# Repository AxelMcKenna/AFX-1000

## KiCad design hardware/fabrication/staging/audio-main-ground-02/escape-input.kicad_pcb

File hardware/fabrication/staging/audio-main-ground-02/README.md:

# AC04 — routed local cells and complete placed-ground continuity

| Top copper | Bottom copper, viewed from below |
| --- | --- |
|  |  |

**The board is not ready for fabrication.** It remains a 150 × 63 × 1.6 mm
four-layer candidate with 328 assigned electrical footprints, four bare test
pads included, and six proposed mounts. U201/ES9292QPRO has no approved land
assignment. Its marked reserve is not a substitute footprint.

**All 131 declared local signal/supply endpoints, all twenty declared local
ground-return pairs, and all 200 placed AGND pads are native-connected.**
The ground reference is protected input terminal J701.2. The earlier 724 open
connections are reduced to **393**; global signal and supply routing is still
unfinished. In2 is reserved for later distribution and has no adopted plane.

| Isolated Linux KiCad 10.0.7 check | Result |
| --- | --- |
| Geometry findings | **0** |
| ERC findings | **0** |
| Schematic parity | **1: missing U201 footprint** |
| Native open connections, uncapped | **393** |
| Ignored DRC / ERC categories | **0 / 0** |
| Tracks / conventional vias | **448 / 199** |
| Placed ground terminals connected to J701.2 | **200 / 200** |

The In1 AGND reference has **8,182.35 mm²** of stored native-filled copper.
Twelve plane openings protect the FDA input/output nodes and the OPA1612
summing nodes on both inner layers. Six full-layer copper exclusions retain
the proposed mounting-hardware allocations. The codec's existing all-layer
reserve remains clear. The [THS4551 layout guidance](https://www.ti.com/lit/gpn/ths4551)
calls for continuous references with openings around sensitive input/output
pins; [OPA1612 layout guidance](https://www.ti.com/lit/ds/symlink/opa1612.pdf)
also addresses grounding and local feedback placement. The 0.5 mm pad and
0.6 mm trace-centre opening margins are project allocations, not manufacturer
specified dimensions or a measured parasitic/stability result.

The 179 added ground vias use 0.60 mm copper lands and 0.30 mm drills. Together
with the twenty retained local signal/supply vias, the fresh native land screen
finds a minimum **0.170 mm** drill-edge-to-SMD-copper gap across both faces,
including same-net lands. No via drill intersects an SMD solder land. Mask
registration/tenting, stencil, plating and the actual stack still need supplier
acceptance. The 182 ground branches include reuse of existing vias. All normal
escape traces retain a 3.5 mm budget; supervisor U205.2 uses a 4.75 mm trace
within its original 5.6 mm local-ground construction allowance. Width remains
0.20 mm. Those lengths exclude travel through the via barrel and do not qualify
current capacity, ground noise or high-frequency return performance.

All amplifier poses and direct compensation capacitor tracks remain unchanged.
The [preceding local rework](../audio-main-local-routing-03/README.md) moves three
unrouted parts. This successor additionally rotates C310 180° in the same body
courtyard, placing its ground terminal outside the congested plane opening.
Its signal terminal remains on the original net. Every conditional body,
floor, upper-board, solder-tail, codec-reserve and support receiving constraint
is renewed; actual mating parts, fasteners, case details and tolerances remain
unapproved. Bare test pads still need explicit non-fitted-copper BOM treatment.

The [independent handoff replay](routing-handoff.json) binds actual copper,
native refill output, per-terminal connectivity and fresh pad geometry. It
checks all pre-existing analog copper, every added branch, all actual drills,
the protected plane openings, and complete ground-terminal coverage. Plane
boundaries use a one-nanometre comparison tolerance matching coordinate
serialization; no copper-clearance or local analog length budget is relaxed.
Executed generation/review source snapshots are retained separately so later
tool development does not rewrite historical evidence.

**Connectivity is not complete power/return, noise, stability, thermal or
manufacturing qualification.** The remaining 393 connections, ESS package and
raw-interface data, physical ADC stars, final parts and harness/mates/supports,
installed power/fault/thermal analysis, inspected Gerber/drill/BOM/placement
outputs and bounded first-article plan must be completed before release. No
supplier request, board order or native Mac CAD launch is made by this work.

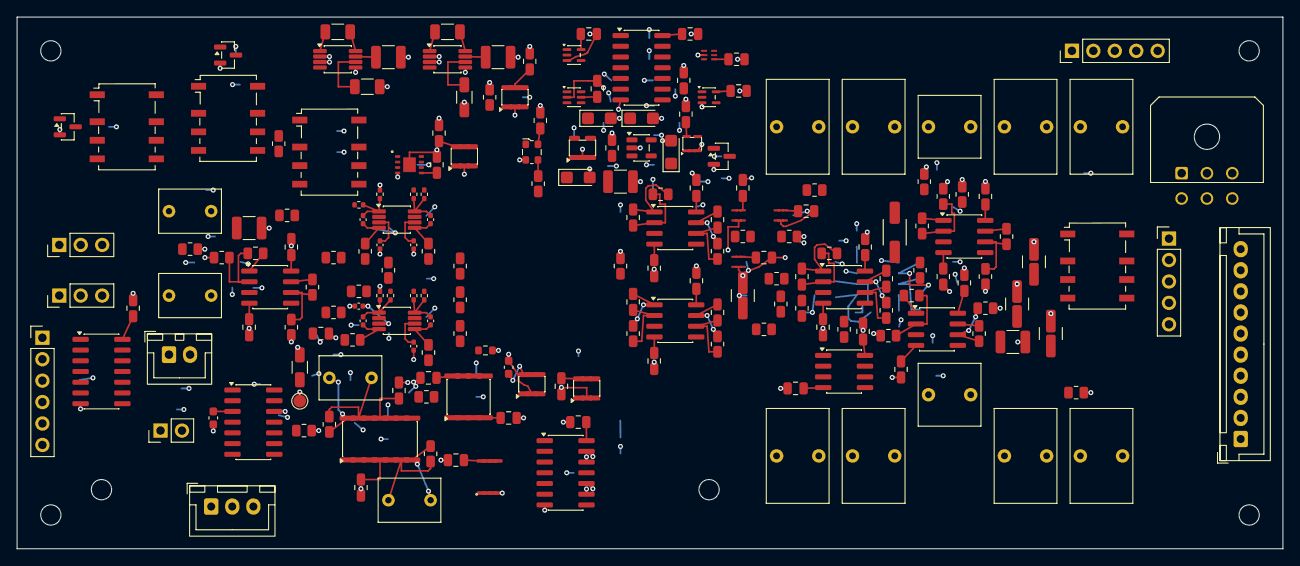
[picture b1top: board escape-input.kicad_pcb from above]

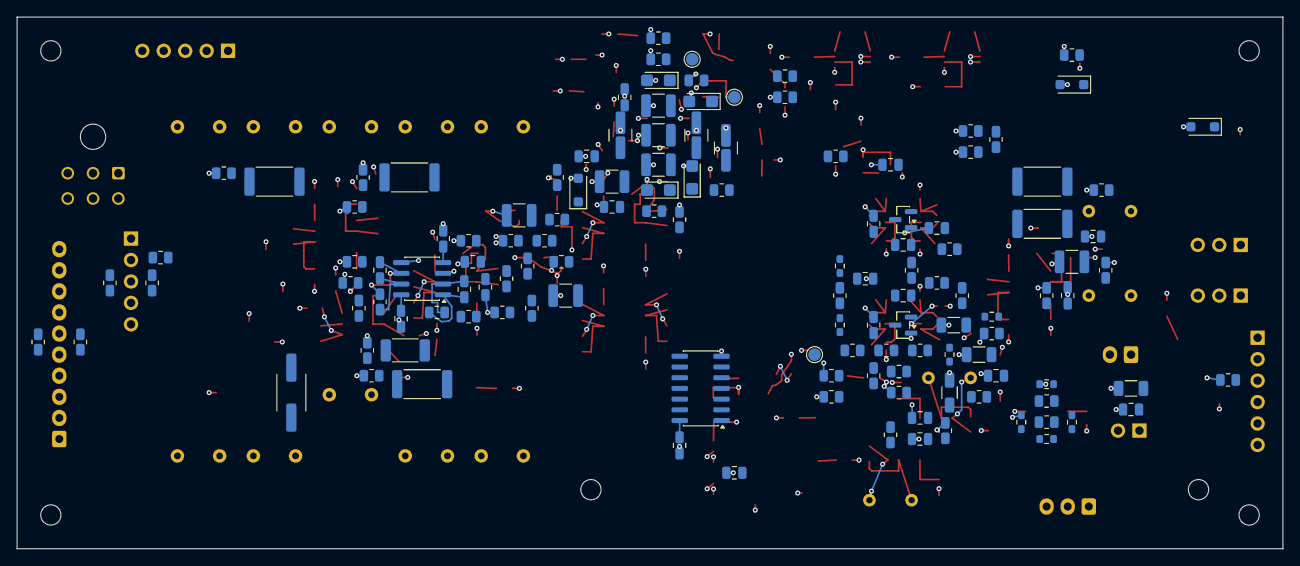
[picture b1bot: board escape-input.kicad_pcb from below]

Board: 4 copper layers, 150.0 x 63.0 mm, 334 parts (129 on the bottom side), 176 nets.

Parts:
C101, C102, C115, C116: 1pF C0G +/-0.1pF; C_0402_1005Metric
C103, C117: 47pF C0G 5%; C_0805_2012Metric
C104, C105, C118, C119: 22pF C0G 5%; C_0805_2012Metric
C106, C120: 100nF 25V X7R; C_0805_2012Metric
C107, C121: 1uF 63V film 10%; C_Rect_L7.2mm_W5.0mm_P5.00mm
C108, C122: 10uF 16V X7R; C_1206_3216Metric
C109, C123: 47uF 25V X7S; C_1210_3225Metric
C110, C111, C124, C125: 47uF 6.3V X7S; C_1206_3216Metric
C112, C126: 2.2uF 16V X7R; C_0805_2012Metric
C113, C114, C127, C128: 100nF 16V X7R; C_0402_1005Metric
C129, C130, C131, C132, C220, C221, C222, C223, C224, C225, C226, C228, C229, C311, C312, C313, C314, C315, C316, C317, C318, C323, C324, C405, C406, C505, C506, C507, C508: 100nF 50V X7R; C_0805_2012Metric
C133, C134: 10uF 50V X7R; C_1206_3216Metric
C135, C136: 100nF 16V X7R; C_0603_1608Metric
C201, C202, C205: 1uF 10V X7R 10%; C_0805_2012Metric
C203, C210, C212, C214: 100nF 50V C0G 5%; C_1210_3225Metric
C204, C206, C207, C208, C209, C211, C213, C215: 1uF 10V tantalum 10%; CP_EIA-3216-18_Kemet-A
C216, C218, C227: 2.2uF 25V X7R 10%; C_1210_3225Metric
C217, C219: 10uF 16V X7R 10%; C_1210_3225Metric
C230, C231, C232, C610, C611, C612: 100nF 16V X7R; C_0805_2012Metric
C301, C302, C306, C307: 510pF 50V C0G 2%; C_0805_2012Metric
C303, C308: 51pF 50V C0G 2%; C_0805_2012Metric
C304, C305, C309, C310: 1nF 50V C0G 1%; C_0805_2012Metric
C319, C320, C509, C510, C511, C512: 10uF 50V X7R; C_1210_3225Metric
C321, C322: 2.2uF film 63V 10%; C_Rect_L7.2mm_W7.2mm_P5.00mm_FKS2_FKP2_MKS2_MKP2
C401, C403: 1uF film 63V 10%; C_Rect_L7.2mm_W5.0mm_P5.00mm
C402, C404: 47pF 50V C0G 5%; C_0805_2012Metric
C407, C408: 10uF 50V X7R 10%; C_1210_3225Metric
C501, C502, C503, C504, C513, C514, C515, C516: 4.7uF film 63V 10%; C_Rect_L7.2mm_W11.0mm_P5.00mm_FKS2_FKP2_MKS2_MKP2
C601: 150pF C0G 5%; C_0805_2012Metric
C602, C603, C604, C605, C606: 100nF X7R; C_0805_2012Metric
C607: 1uF 16V X7R; C_0805_2012Metric
C608: 22uF 16V X7R; C_1206_3216Metric
C609: 1uF 16V X7R 10%; C_0805_2012Metric
D101, D102: BAT54S,215; SOT-23
D601, D602, D603: SMF9.0A; D_SOD-123F
H1, H2, H3, H4: M2_CLEARANCE; M2_Clearance
H5, H6: M2_SHARED_SUPPORT; M2_Clearance
J203, J603: Conn_01x05; PinHeader_1x05_P2.54mm_Vertical
J402: B10B-XH-A(LF)(SN); JST_XH_B10B-XH-A_1x10_P2.50mm_Vertical
J403: B3B-XH-A(LF)(SN); JST_XH_B3B-XH-A_1x03_P2.50mm_Vertical
J602: Conn_01x06; PinHeader_1x06_P2.54mm_Vertical
J606: Conn_01x02; PinHeader_1x02_P2.54mm_Vertical
J607, J608: Conn_01x03; PinHeader_1x03_P2.54mm_Vertical
J701: 43045-0600; Molex_Micro-Fit_3.0_43045-0600_2x03_P3.00mm_Horizontal
J702: B2B-XH-A(LF)(SN); JST_XH_B2B-XH-A_1x02_P2.50mm_Vertical
K401, K503, K601, K602: G6K-2F-Y DC5; Relay_DPDT_Omron_G6K-2F-Y
Q601, Q602, Q603: AO3400A; SOT-23
R101, R102, R117, R118: 2.49k 0.05%; R_0402_1005Metric
R103, R104, R119, R120: 1.21k 0.05%; R_0402_1005Metric
R105, R106, R121, R122: 3.3R 1%; R_0805_2012Metric
R107, R123: 1M 1%; R_0805_2012Metric
R108, R109, R124, R125: 100k 0.01%; R_0805_2012Metric
R110, R111, R126, R127, R212: 10k 0.1%; R_0805_2012Metric
R112, R128: 10M 1%; R_0805_2012Metric
R113, R129, R203, R204, R601, R606: 10k 1%; R_0805_2012Metric
R114, R130, R205, R206, R603, R604, R605, R607, R615: 47k 1%; R_0805_2012Metric
R115, R131: 68k 1%; R_0805_2012Metric
R116, R132: 0.1R 1%; R_0805_2012Metric
R133: 1k 1%; R_0805_2012Metric
R134, R136: 100k 0.01%; R_0603_1608Metric
R135, R137, R139, R141: 10k 0.01%; R_0603_1608Metric
R138: 161k 0.01%; R_0805_2012Metric
R140: 240k 0.01%; R_0805_2012Metric
R142, R143: 10k 1%; R_0603_1608Metric
R144: 100k 1%; R_0603_1608Metric
R201, R202: 2k 1%; R_0805_2012Metric
R207, R208, R209, R210, R517, R518, R602, R617, R618: 100k 1%; R_0805_2012Metric
R211: 27.7k 0.1%; R_0805_2012Metric
R213, R214, R215, R216: 33 1%; R_0805_2012Metric
R301, R302, R313, R314: 1.8k 0.1%; R_0805_2012Metric
R303, R304, R315, R316: 4.3 1%; R_0805_2012Metric
R305, R306, R317, R318: 100k 0.1%; R_0805_2012Metric
R307, R319: 1.2M 0.1%; R_0805_2012Metric
R308, R309, R310, R311, R320, R321, R322, R323: 499 0.01%; R_0805_2012Metric
R312, R324, R407, R414: 33.2 0.1%; R_0805_2012Metric
R325, R326, R401, R408: 33.2k 0.1%; R_0805_2012Metric
R327, R328: 2.74k 0.1% 0.5W; R_2010_5025Metric
R402, R409: 13.7k 0.1%; R_0805_2012Metric
R403, R410: 4.99k 0.1% 1W; R_2512_6332Metric
R404, R411: 68k 0.1%; R_0805_2012Metric
R405, R412: 365 0.1%; R_0805_2012Metric
R406, R413, R502, R506: 1k 0.1%; R_0805_2012Metric
R501, R505: 5.23k 0.1%; R_0805_2012Metric
R503, R507, R511, R515: 100 1% 1W; R_2512_6332Metric
R504, R508, R512, R516: 20k 1%; R_0805_2012Metric
R509, R513: 1.21k 0.1%; R_0805_2012Metric
R510, R514: 2k 0.1%; R_0805_2012Metric
R608, R610, R612: 4.7k 1%; R_0805_2012Metric
R609, R611, R613: 270k 1%; R_0805_2012Metric
R614: 383k 0.1% 25ppm; R_0805_2012Metric
R616: 147k 1%; R_0805_2012Metric
TP401: TEST_ONLY_ADC_DRV_ENABLE; TestPoint_Pad_D1.5mm
TP402: TEST_ONLY_CHIP_EN; TestPoint_Pad_D1.5mm
TP403: TEST_ONLY_PD_GATED; TestPoint_Pad_D1.5mm
TP404: TEST_ONLY_AGND; TestPoint_Pad_D1.5mm
U101, U102: THS4551IDGKR; VSSOP-8_3x3mm_P0.65mm
U103, U305, U401: OPA1656ID; SOIC-8_3.9x4.9mm_P1.27mm
U104: OPA4192ID; SOIC-14_3.9x8.7mm_P1.27mm
U105, U106: LM7705MM/NOPB; VSSOP-8_3x3mm_P0.65mm
U107: TLV9024DR; SOIC-14_3.9x8.7mm_P1.27mm
U108, U605: TPS3808G50DBVR; SOT-23-6
U202: TPS7A2033PDBVR; SOT-23-5
U203: TPS7A2045PDBVR; SOT-23-5
U204, U205, U208: TPS389033DSET; TI_DSE0006A_TPS3890
U206: TPS389001DSET; TI_DSE0006A_TPS3890
U207, U602, U606: SN74HCS08DR; SOIC-14_3.9x8.7mm_P1.27mm
U209, U212: SN74LVC1G08DCKR; SOT-353_SC-70-5
U210: SN74LVC2G17DCKR; SOT-363_SC-70-6
U211: SN74LVC1G17DCKR; SOT-353_SC-70-5
U301, U302, U303, U304, U502: OPA1612AID; SOIC-8_3.9x4.9mm_P1.27mm
U501: OPA2992D; SOIC-8_3.9x4.9mm_P1.27mm
U601: TPS3431SDRBR; TI_DRB0008A_TPS3431
U603: SN74LVC1G74DCTR; TI_DCT0008A_SN74LVC1G74
U604: TPS3808G33DBVR; SOT-23-6
U607: LTC6994HS6-1#TRMPBF; TSOT-23-6
U608: SN74HCS86DR; SOIC-14_3.9x8.7mm_P1.27mm
Y201: ECS-2520MVLC-245.7-BN-TR; Oscillator_SMD_ECS_2520MV-xxx-xx-4Pin_2.5x2.0mm

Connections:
5V_DIG: C608.1, J702.1, K401.1, K503.1, K601.1, K602.1, U605.5
/ADC/BIAS_SHIFT_L: R134.2, R135.1, U107.4, U107.7
/ADC/BIAS_SHIFT_R: R136.2, R137.1, U107.8, U107.11
/ADC/BUF_L: R101.1, U103.1, U103.2
/ADC/BUF_R: R117.1, U103.6, U103.7
/ADC/CM_DRIVE_L: C107.1, R112.1, R113.1, U104.7
/ADC/CM_DRIVE_R: C121.1, R128.1, R129.1, U104.14
/ADC/CM_SENSE_L: C107.2, R110.2, R111.2, R112.2, U104.6
/ADC/CM_SENSE_R: C121.2, R126.2, R127.2, R128.2, U104.13
/ADC/DRV_LN: C101.1, R106.1, U101.5
/ADC/DRV_LP: C102.1, R105.1, U101.4
/ADC/DRV_RN: C115.1, R122.1, U102.5
/ADC/DRV_RP: C116.1, R121.1, U102.4
/ADC/FB_N_L: C102.2, R102.2, R104.2, U101.1
/ADC/FB_N_R: C116.2, R118.2, R120.2, U102.1
/ADC/FB_P_L: C101.2, R101.2, R103.2, U101.8
/ADC/FB_P_R: C115.2, R117.2, R119.2, U102.8
/ADC/FLY_N_L: C108.2, U105.8
/ADC/FLY_N_R: C122.2, U106.8
/ADC/FLY_P_L: C108.1, U105.1
/ADC/FLY_P_R: C122.1, U106.1
/ADC/NBIAS_L: C111.1, C114.1, J403.2, R115.2, R116.2, R135.2, U101.6
/ADC/NBIAS_R: C125.1, C128.1, J403.3, R131.2, R132.2, R137.2, U102.6
/ADC/NPUMP_L: C110.1, R116.1, U105.6
/ADC/NPUMP_R: C124.1, R132.1, U106.6
/ADC/PD_GATED: R114.1, R130.1, R143.2, R144.1, TP403.1, U108.1
/ADC/PD_L: R114.2, R115.1, U101.7
/ADC/PD_R: R130.2, R131.1, U102.7
/ADC/REF_DIV_L: C106.1, R108.2, R109.1, U104.3
/ADC/REF_DIV_R: C120.1, R124.2, R125.1, U104.10
/ADC/REF_HALF_L: U104.1, U104.2, U104.5
/ADC/REF_HALF_R: U104.8, U104.9, U104.12
/ADC/RES_L: C109.1, U105.7
/ADC/RES_R: C123.1, U106.7
/ADC/THRESH_LOWER: R140.2, R141.1, U107.6, U107.10
/ADC/THRESH_UPPER: R138.2, R139.1, U107.5, U107.9
/ADC/VOCM_L: D101.3, R113.2, U101.2
/ADC/VOCM_R: D102.3, R129.2, U102.2
/BYPASS/ARMED: J602.5, U602.9, U603.3
/BYPASS/BYPASS_GATE: Q601.1, R608.2, R609.1
/BYPASS/BYPASS_LOW: D601.1, K601.8, Q601.3
/BYPASS/BYPASS_SENSE: J602.6, J603.5, R606.2
/BYPASS/CLEAR_N: U603.6, U606.5, U606.8
/BYPASS/COIL_ENABLE: U602.8, U606.4
/BYPASS/CWD: C601.1, U601.2
/BYPASS/FINAL_ENABLE: R608.1, U606.6
/BYPASS/GAIN_DELAY: C609.1, R615.2, U608.2
/BYPASS/GAIN_EDGE: U608.3, U608.4
/BYPASS/GAIN_GATE: Q602.1, R610.2, R611.1
/BYPASS/GAIN_REQ: J602.4, R607.1, R610.1, R615.1, U608.1
/BYPASS/GAIN_STABLE: U606.13, U608.6
/BYPASS/HEARTBEAT: J602.2, R602.1, U601.6
/BYPASS/INPUT_ENABLE: R612.1, U602.3, U602.4, U606.12
/BYPASS/INPUT_GATE: Q603.1, R612.2, R613.1
/BYPASS/INPUT_LOW: D603.1, K602.8, Q603.3
/BYPASS/INPUT_READY: J606.2, U606.3, U606.9
/BYPASS/IN_L: J607.1, K601.2, K602.4
/BYPASS/IN_R: J607.3, K601.7, K602.5
/BYPASS/LOCAL_OK: R601.2, U601.7, U601.8, U602.1, U604.1, U605.1
/BYPASS/MCU_PERMIT: J602.3, R603.1, U602.12, U602.13
/BYPASS/OUT_L: J608.1, K601.3
/BYPASS/OUT_R: J608.3, K601.6
/BYPASS/PERMIT_CLEAN: U602.10, U602.11, U603.1
/BYPASS/PROCESS_HEALTH: U602.6, U606.10
/BYPASS/PROCESS_OK: J603.2, R604.1, U602.5
/BYPASS/STARTUP_CT: R618.2, U604.4
/BYPASS/TIMER_DIV: R616.2, R617.1, U607.4
/BYPASS/TIMER_ENABLE: U606.1, U606.11, U607.1
/BYPASS/TIMER_INPUT_OK: U606.2, U607.6
/BYPASS/TIMER_SET: R614.1, U607.3
/CODEC/A3V3: C205.1, C217.1, C229.1, U202.5, U205.1
/CODEC/A4V5: C207.1, C219.1, R211.1, U203.5
/CODEC/ADC_BIAS_IO: U211.4, U212.2
/CODEC/ADC_DATA: J203.4, R216.2
/CODEC/BCLK: J203.2, R214.2
/CODEC/CHIP_REQUEST: U207.6, U210.1
/CODEC/CLK_VALID: R207.1, U207.9
/CODEC/CODEC_FLAGS: U207.8, U207.13
/CODEC/CODEC_PGOOD: J402.9, R203.1, U204.6, U205.6, U206.6, U207.1
/CODEC/CODEC_RUN: J402.5, R205.1, U207.5
/CODEC/CT_SETTLE: C227.1, U208.5
/CODEC/DRIVER_SETTLE_READY: U208.3, U209.1, U212.4
/CODEC/MCLK_SRC: R213.1, Y201.3
/CODEC/PRE_ANALOG_OK: J402.8, R206.1, U207.2
/CODEC/RAMP_DONE: R208.1, U207.10
/CODEC/REF_DAC_BUF: C203.1, C204.1
/CODEC/REF_PLL: C210.1, C211.1
/CODEC/SCL: J402.3, R201.1
/CODEC/SDA: J402.4, R202.1
/CODEC/SENSE_4V5: R211.2, R212.1, U206.1
/CODEC/SETTLE_ENABLE: U207.11, U210.3, U212.1
/CODEC/SUPPLY_OK: U207.3, U207.4
/CODEC/TIMER_OK: R204.1, U208.6, U209.2
/CODEC/WS: J203.3, R215.2
/DAC/BIAS_N_L: R304.2, U301.5
/DAC/BIAS_N_R: R316.2, U302.5
/DAC/BIAS_P_L: R303.2, U301.3
/DAC/BIAS_P_R: R315.2, U302.3
/DAC/BUF_IN_L: R327.2, U305.3
/DAC/BUF_IN_R: R328.2, U305.5
/DAC/BUF_OUT_L: R312.1, U305.1, U305.2
/DAC/BUF_OUT_R: R324.1, U305.6, U305.7
/DAC/CM_DRV_L: C303.2, R303.1, R304.1, R307.2, U303.1
/DAC/CM_DRV_R: C308.2, R315.1, R316.1, R319.2, U303.7
/DAC/CM_SUM_L: C303.1, R305.2, R306.2, R307.1, U303.2
/DAC/CM_SUM_R: C308.1, R317.2, R318.2, R319.1, U303.6
/DAC/HP_NODE_L: C321.2, R325.1, R327.1
/DAC/HP_NODE_R: C322.2, R326.1, R328.1
/DAC/IV_N_L: C302.2, R302.2, R306.1, R309.1, U301.7
/DAC/IV_N_R: C307.2, R314.2, R318.1, R321.1, U302.7
/DAC/IV_P_L: C301.2, R301.2, R305.1, R308.1, U301.1
/DAC/IV_P_R: C306.2, R313.2, R317.1, R320.1, U302.1
/DAC/RX_NEG_L: C304.1, R308.2, R310.1, U304.2
/DAC/RX_NEG_R: C309.1, R320.2, R322.1, U304.6
/DAC/RX_OUT_L: C304.2, C321.1, R310.2, U304.1
/DAC/RX_OUT_R: C309.2, C322.1, R322.2, U304.7
/DAC/RX_POS_L: C305.1, R309.2, R311.1, U304.3
/DAC/RX_POS_R: C310.1, R321.2, R323.1, U304.5
/INPUT/ATTN_L: K401.2, R401.2, R402.1
/INPUT/ATTN_R: K401.7, R408.2, R409.1
/INPUT/BUF_IN_L: C401.2, C402.1, R404.1, U401.3
/INPUT/BUF_IN_R: C403.2, C404.1, R411.1, U401.5
/INPUT/BUF_OUT_L: R405.2, R407.1, U401.1
/INPUT/BUF_OUT_R: R412.2, R414.1, U401.7
/INPUT/GAIN_FB_L: R405.1, R406.1, U401.2
/INPUT/GAIN_FB_R: R412.1, R413.1, U401.6
/INPUT/HP_SRC_L: C401.1, R403.2
/INPUT/HP_SRC_R: C403.1, R410.2
/INPUT/RANGE_L: K401.3, R403.1
/INPUT/RANGE_R: K401.6, R410.1
/OUTPUT/M_AC_L: C501.2, C513.2, K503.2, R504.1
/OUTPUT/M_AC_R: C502.2, C514.2, K503.7, R508.1
/OUTPUT/M_DRV_L: R501.2, R503.1, U501.1
/OUTPUT/M_DRV_R: R505.2, R507.1, U501.7
/OUTPUT/M_FB_L: R501.1, R502.1, U501.2
/OUTPUT/M_FB_R: R505.1, R506.1, U501.6
/OUTPUT/M_SER_L: C501.1, C513.1, R503.2
/OUTPUT/M_SER_R: C502.1, C514.1, R507.2
/OUTPUT/S_AC_L: C503.2, C515.2, K503.4, R512.1
/OUTPUT/S_AC_R: C504.2, C516.2, K503.5, R516.1
/OUTPUT/S_DRV_L: R509.2, R511.1, U502.1
/OUTPUT/S_DRV_R: R513.2, R515.1, U502.7
/OUTPUT/S_FB_L: R509.1, R510.1, U502.2
/OUTPUT/S_FB_R: R513.1, R514.1, U502.6
/OUTPUT/S_SER_L: C503.1, C515.1, R511.2
/OUTPUT/S_SER_R: C504.1, C516.1, R515.2
ADC_BIAS_WINDOW_OK: R142.2, U107.1, U107.2, U107.13, U107.14, U108.3, U211.2
ADC_DRV_ENABLE: R143.1, TP401.1, U210.4
ADC_LN: C103.2, C105.1, R103.1, R106.2, R111.1
ADC_LP: C103.1, C104.1, R104.1, R105.2, R110.1
ADC_RN: C117.2, C119.1, R119.1, R122.2, R127.1
ADC_RP: C117.1, C118.1, R120.1, R121.2, R126.1
AGND: C104.2, C105.2, C106.2, C109.2, C110.2, C111.2, C112.2, C113.2, C114.2, C118.2, C119.2, C120.2, C123.2, C124.2, C125.2, C126.2, C127.2, C128.2, C129.2, C130.2, C131.2, C132.2, C133.2, C134.2, C135.2, C136.2, C201.2, C202.2, C203.2, C204.2, C205.2, C206.2, C207.2, C208.2, C209.2, C210.2, C211.2, C212.2, C213.2, C214.2, C215.2, C216.2, C217.2, C218.2, C219.2, C220.2, C221.2, C222.2, C223.2, C224.2, C225.2, C226.2, C227.2, C228.2, C229.2, C230.2, C231.2, C232.2, C305.2, C310.2, C311.2, C312.2, C313.2, C314.2, C315.2, C316.2, C317.2, C318.2, C319.2, C320.2, C323.2, C324.2, C402.2, C404.2, C405.2, C406.2, C407.2, C408.2, C505.2, C506.2, C507.2, C508.2, C509.2, C510.2, C511.2, C512.2, C601.2, C602.2, C603.2, C604.2, C605.2, C606.2, C607.2, C608.2, C609.2, C610.2, C611.2, C612.2, D101.1, D102.1, D601.2, D602.2, D603.2, J203.1, J402.1, J402.7, J403.1, J602.1, J603.4, J606.1, J607.2, J608.2, J701.2, J702.2, Q601.2, Q602.2, Q603.2, R102.1, R107.2, R109.2, R118.1, R123.2, R125.2, R133.2, R139.2, R141.2, R144.2, R205.2, R206.2, R207.2, R208.2, R209.2, R210.2, R212.2, R311.2, R323.2, R325.2, R326.2, R402.2, R404.2, R406.2, R409.2, R411.2, R413.2, R502.2, R504.2, R506.2, R508.2, R510.2, R512.2, R514.2, R516.2, R517.2, R518.2, R602.2, R603.2, R604.2, R605.2, R607.2, R609.2, R611.2, R613.2, R614.2, R617.2, TP404.1, U105.2, U105.3, U105.5, U106.2, U106.3, U106.5, U107.12, U108.2, U202.2, U203.2, U204.2, U205.2, U206.2, U207.7, U208.2, U209.3, U210.2, U211.3, U212.3, U303.3, U303.5, U601.4, U601.9, U602.7, U603.4, U604.2, U605.2, U606.7, U607.2, U608.7, U608.9, U608.10, U608.12, U608.13, Y201.2
ANALOG_OK: J402.6, J402.10, J603.3, R210.1, R605.1, U209.4, U602.2
CHIP_EN: R209.1, TP402.1, U207.12, U210.6
DAC_LN: C302.1, R302.1, U301.6
DAC_LP: C301.1, R301.1, U301.2
DAC_RN: C307.1, R314.1, U302.6
DAC_RP: C306.1, R313.1, U302.2
GAIN_LOW: D602.1, K401.8, K503.8, Q602.3
N12: C130.1, C132.1, C134.1, C312.1, C314.1, C316.1, C318.1, C320.1, C324.1, C406.1, C408.1, C508.1, C512.1, J701.5, U103.4, U104.11, U301.4, U302.4, U303.4, U304.4, U305.4, U401.4, U502.4
N19: C506.1, C510.1, J701.3, U501.4
P12: C129.1, C131.1, C133.1, C311.1, C313.1, C315.1, C317.1, C319.1, C323.1, C405.1, C407.1, C507.1, C511.1, J701.4, U103.8, U104.4, U301.8, U302.8, U303.8, U304.8, U305.8, U401.8, U502.8
P19: C505.1, C509.1, J701.1, U501.8
PRE_OUT_L: R107.1, R407.2, U103.3
PRE_OUT_R: R123.1, R414.2, U103.5
PROC_IN_L: K401.4, K602.3, R401.1
PROC_IN_R: K401.5, K602.6, R408.1
PROC_OUT_L: K503.3, K601.4
PROC_OUT_R: K503.6, K601.5
RECV_L: R312.2, R517.1, U501.3, U502.3
RECV_R: R324.2, R518.1, U501.5, U502.5
REF_ADC1: C212.1, C213.1, R108.1
REF_ADC2: C214.1, C215.1, R124.1
V3V3_IO: C201.1, C220.1, C221.1, C222.1, C223.1, C224.1, C225.1, C226.1, C228.1, C230.1, C231.1, C232.1, C602.1, C603.1, C604.1, C605.1, C606.1, C607.1, C610.1, C611.1, C612.1, J402.2, J603.1, R201.2, R202.2, R203.2, R204.2, R601.1, R606.1, R616.1, R618.1, U204.1, U204.3, U204.4, U205.3, U205.4, U206.3, U206.4, U207.14, U208.1, U208.4, U209.5, U210.5, U211.5, U212.5, U601.1, U601.3, U601.5, U602.14, U603.2, U603.7, U603.8, U604.3, U604.5, U604.6, U605.3, U605.6, U606.14, U607.5, U608.5, U608.14, Y201.1, Y201.4
V5_REG: C112.1, C113.1, C126.1, C127.1, C135.1, C136.1, C216.1, C218.1, D101.2, D102.2, J701.6, R133.1, R134.1, R136.1, R138.1, R140.1, R142.1, U101.3, U102.3, U105.4, U106.4, U107.3, U108.5, U108.6, U202.1, U202.3, U203.1, U203.3
